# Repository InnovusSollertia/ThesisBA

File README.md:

# OptiREX

Used elements:
- STM32H750VBT6x - CortexM7 microcontroller
- ST7789 - IPS Display with 240x240 resolution
- TFDU-4101 - IrDa tranciver/recever
- 2x and 4x LEDs - indication of connection and power systems
- 2x Li-Ion battery

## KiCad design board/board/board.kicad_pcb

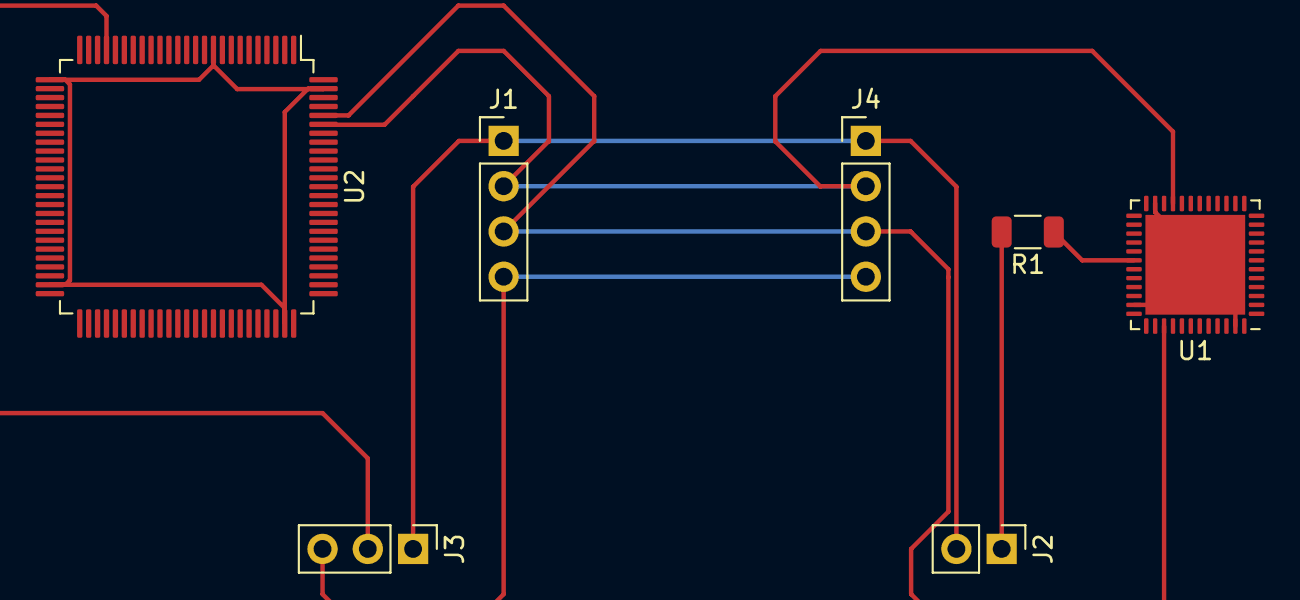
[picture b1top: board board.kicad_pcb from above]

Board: 2 copper layers, 7 parts (0 on the bottom side), 7 nets.

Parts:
J1, J4: Conn_01x04; PinHeader_1x04_P2.54mm_Vertical
J2: Conn_01x02; PinHeader_1x02_P2.54mm_Vertical
J3: Conn_01x03; PinHeader_1x03_P2.54mm_Vertical
R1: 10K; R_1206_3216Metric
U1: STM32F411CEUx; QFN-48-1EP_7x7mm_P0.5mm_EP5.6x5.6mm
U2: STM32H750VBTx; LQFP-100_14x14mm_P0.5mm

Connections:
+5V: J1.4, J3.3, J4.4
/SCL: J1.2, J4.2, U1.21 (PB10), U2.95 (PB8)
/SDA: J1.3, J4.3, U1.39 (PB3), U2.96 (PB9)
/SIGNAL: J3.2, U2.22 (PA0)
GND: J1.1, J2.2, J3.1, J4.1
unnamed: J2.1, R1.2
unnamed: R1.1, U1.30 (PA9), U1.48 (VDD)

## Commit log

2022-12-18 20221218_130850
2022-12-22 20221222_094500
2022-12-22 20221222_121840
2022-12-24 20221224_115000
2023-01-14 20230114_151200
2023-01-23 20230123_145320
2023-04-13 20230413_081659
2023-04-13 20230413_082240
2023-04-13 20230413_082730
2023-04-14 20230414_100300
2023-04-22 20230422_1240
2023-04-25 20230425_090830
2023-05-07 20230507_1900
2023-05-10 new branch
2023-05-11 upload more `docs`
2023-05-15 20230516_0025
2023-05-16 20230516_2036
2023-05-17 20230517_2118
2023-05-18 20230518_1408
2023-05-19 20230519_1209
2023-05-25 20230525_1954
2023-06-01 20230601_0820
2023-06-01 20230601_1056
2023-06-01 20230601_1058
2023-06-06 20230606_1355
2023-06-07 20230607_1822
2023-06-10 20230610_1713
2023-06-11 20230611_2359
2023-06-11 20230612_0008
2023-06-11 20230612_0010
2023-06-13 20230613_1043
2023-08-04 20230804_0946
